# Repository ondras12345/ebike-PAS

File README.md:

# e-bike PAS signal generator
Eunorau Sin-wave LD-FXK-038 e-bike controller is often used on electric kick
scooters, but those don't have pedals, so you cannot make use of the pedal
assist (PAS) feature. This simple device generates a valid pedalling signal to
achieve cruise control-like functionality.

## Usage
Hold the start button for at least 2 seconds to enable PAS. Start braking to
turn it off.

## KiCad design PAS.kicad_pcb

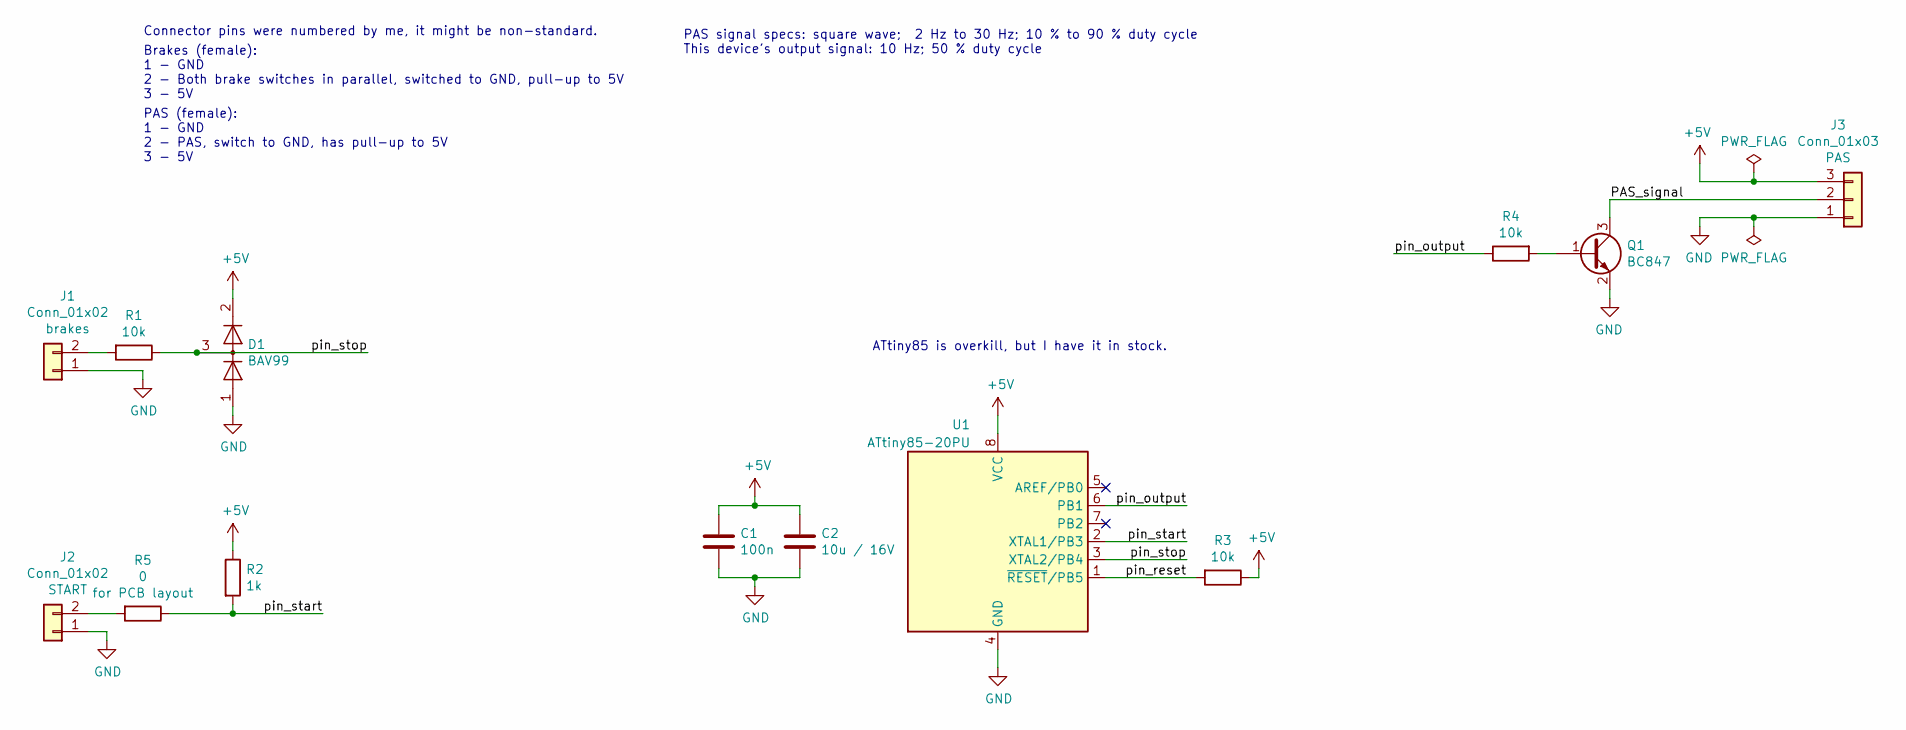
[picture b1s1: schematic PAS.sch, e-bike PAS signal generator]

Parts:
C1: 100n; C_1206_3216Metric_Pad1.33x1.80mm_HandSolder
C2: 10u / 16V; C_1206_3216Metric_Pad1.33x1.80mm_HandSolder
D1: BAV99; SOT-23
J1, J2: Conn_01x02; PinHeader_1x02_P2.54mm_Vertical
J3: Conn_01x03; PinHeader_1x03_P2.54mm_Vertical
Q1: BC847; SOT-23
R1, R3, R4: 10k; R_1206_3216Metric_Pad1.30x1.75mm_HandSolder
R2: 1k; R_1206_3216Metric_Pad1.30x1.75mm_HandSolder
R5: 0; R_1206_3216Metric_Pad1.30x1.75mm_HandSolder
U1: ATtiny85-20PU; DIP-8_W7.62mm

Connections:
+5V: C1.1, C2.1, D1.2 (A), J3.3, R2.1, R3.1, U1.8 (VCC)
/PAS_signal: J3.2, Q1.3 (C)
/pin_output: R4.1, U1.6 (PB1)
/pin_reset: R3.2, U1.1 (~RESET~/PB5)
/pin_start: R2.2, R5.1, U1.2 (XTAL1/PB3)
/pin_stop: D1.3 (K), R1.1, U1.3 (XTAL2/PB4)
GND: C1.2, C2.2, D1.1 (K), J1.1, J2.1, J3.1, Q1.2 (E), U1.4 (GND)
unnamed: J1.2, R1.2
unnamed: J2.2, R5.2
unnamed: Q1.1 (B), R4.2

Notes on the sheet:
Brakes (female): 1 - GND 2 - Both brake switches in parallel, switched to GND, pull-up to 5V 3 - 5V
Connector pins were numbered by me, it might be non-standard.
PAS (female): 1 - GND 2 - PAS, switch to GND, has pull-up to 5V 3 - 5V
PAS signal specs: square wave; 2 Hz to 30 Hz; 10 % to 90 % duty cycle This device's output signal: 10 Hz; 50 % duty cycle
ATtiny85 is overkill, but I have it in stock.

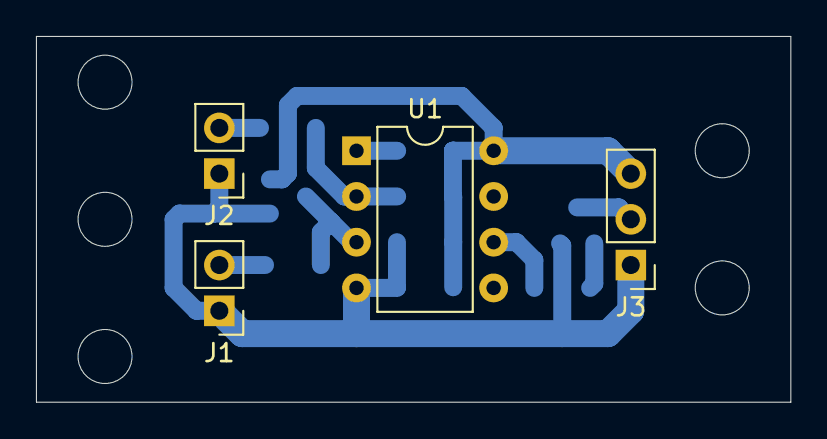
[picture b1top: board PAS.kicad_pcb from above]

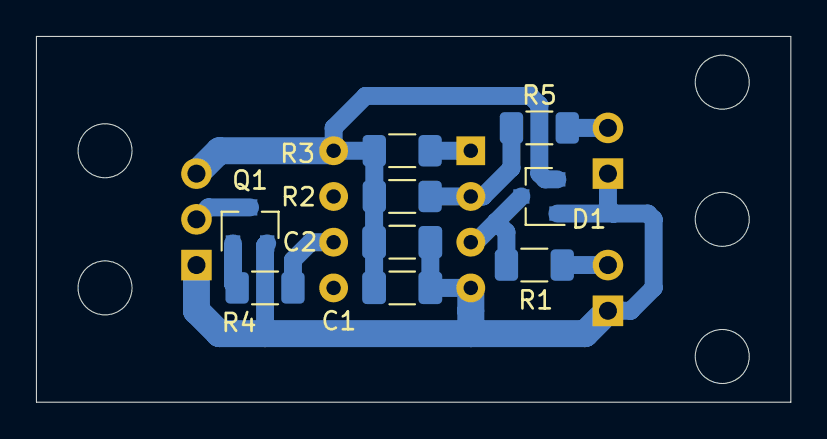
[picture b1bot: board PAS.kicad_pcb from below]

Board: 2 copper layers, 41.9 x 20.3 mm, 13 parts (9 on the bottom side), 10 nets.

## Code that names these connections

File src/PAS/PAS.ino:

/*
ATtiny core:
- http://drazzy.com/package_drazzy.com_index.json
- https://github.com/SpenceKonde/ATTinyCore
Board: ATtiny25/45/85 (no bootloader)
Chip: ATtiny85
Clock Source: 1MHz (internal)
Timer1 Clock: CPU (CPU frequency)
LTO: Enabled
millis()/micros(): Enabled
Save EEPROM: EEPROM Retained
B.O.D. Level: B.O.D. Enabled (4.3V)

Burn Bootloader first to set fuses, than Upload Using Programmer.
*/

// https://github.com/PaulStoffregen/TimerOne
// you need to get it from Git (commit
// 756a4b3cf4bd77c8f53483ede2ea0e245409c624 needs to be applied)
#include <TimerOne.h>

#define pin_start 3  // active low
#define pin_stop 4  // active low
#define pin_output 1

#define start_hold_time 2000  // ms
// 10Hz --> 0.1s:
#define output_period 100000  // us


bool running = false;
unsigned long start_prev_millis = 0;
bool prev_pin_start = true;  // active low


void setup()
{
    pinMode(pin_start, INPUT);
    pinMode(pin_stop, INPUT);
    pinMode(pin_output, OUTPUT);

    /* If the start button is held at the time of startup, wait for it to be
    released (in case it was shorted or something). */
    delay(500);
    while(!digitalRead(pin_start));

    Timer1.initialize(output_period / 2);
    Timer1.attachInterrupt(timer1_interrupt);
    Timer1.stop();
    digitalWrite(pin_output, LOW);
}


void loop()
{
    if (!digitalRead(pin_stop) && running)
    {
        running = false;
        Timer1.stop();
        digitalWrite(pin_output, LOW);
    }


    if (running) return;

    // Treat pin_start as HIGH (not pressed) if pin_stop is LOW
    bool curr_pin_start = digitalRead(pin_start) || !digitalRead(pin_stop);

    if (!curr_pin_start && prev_pin_start)
        start_prev_millis = millis();

    if (!curr_pin_start && (millis() - start_prev_millis) >= start_hold_time)
    {
        running = true;
        Timer1.start();
    }

    prev_pin_start = curr_pin_start;
}


void timer1_interrupt()
{
    static bool output_state = false;
    output_state = !output_state;
    digitalWrite(pin_output, output_state);
}

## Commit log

2023-06-21 Add project files
2023-06-22 Create LICENSE
